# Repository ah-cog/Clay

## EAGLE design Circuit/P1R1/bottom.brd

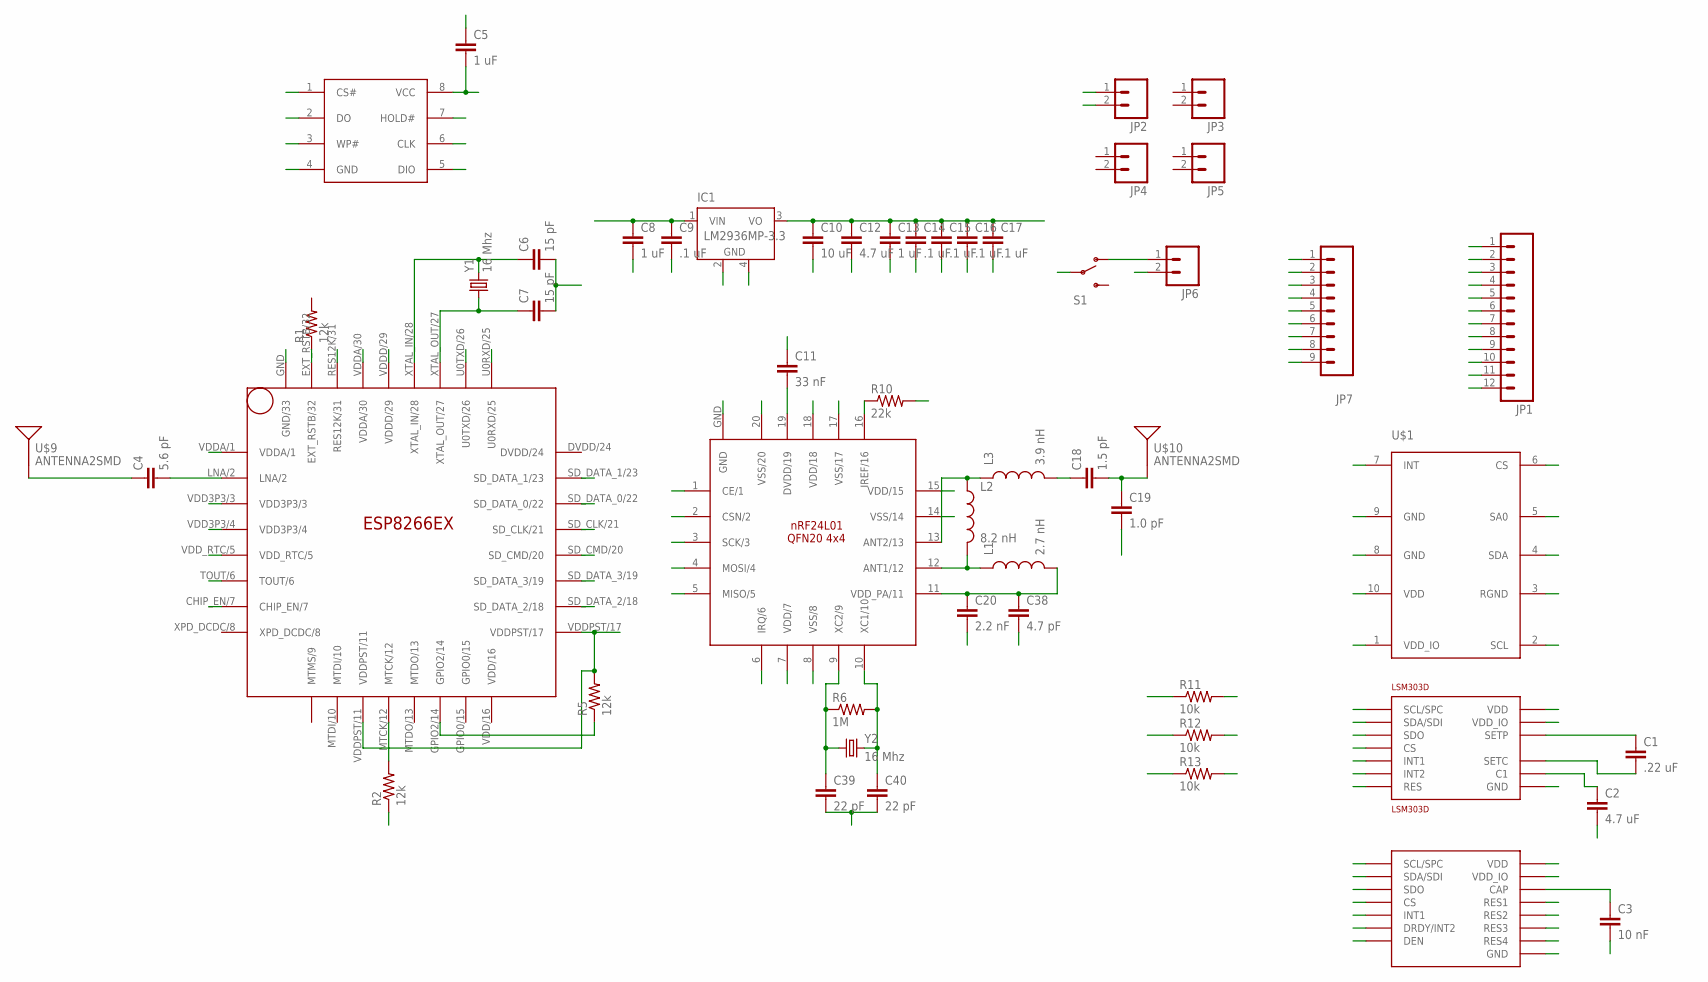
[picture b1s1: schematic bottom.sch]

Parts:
C1: .22 uF; 0603-CAP
C2, C12: 4.7 uF; 0603-CAP
C3: 10 nF; 0603-CAP
C4: 5.6 pF; 0603-CAP
C5, C8, C13: 1 uF; 0603-CAP
C6, C7: 15 pF; 0603-CAP
C9, C14, C15, C16, C17: .1 uF; 0603-CAP
C10: 10 uF; 0603-CAP
C11: 33 nF; 0603-CAP
C18: 1.5 pF; 0603-CAP
C19: 1.0 pF; 0603-CAP
C20: 2.2 nF; 0603-CAP
C38: 4.7 pF; 0603-CAP
C39, C40: 22 pF; 0603-CAP
IC1: LM2936MP-3.3; SOT223
JP1: M12PTH; 1X12
JP2, JP3, JP4, JP5, JP6: M02LOCK; 1X02_LOCK
JP7: M09; 1X09
L1: 2.7 nH; C0402
L2: 8.2 nH; C0402
L3: 3.9 nH; C0402
LSM303D: LSM303D; LGA16L
MESH: NRF24L01; QFN20(4X4)
R1, R2, R5: 12k; 0603-RES
R6: 1M; 0603-RES
R10: 22k; 0603-RES
R11, R12, R13: 10k; 0603-RES
S1: SWITCH-SPDT-SMD-A; SWITCH-SPST-SMD-A
U$1: LPS25H
U$2: L3GD20H; LGA16L
U$3: 25Q40; SOP8
U$9, U$10: ANTENNA2SMD; ANTENNA-CHIP2
WIFI: ESP8266EX; QFN32
Y1, Y2: 16 Mhz; CRYSTAL-SMD-5X3

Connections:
CE: JP7.3, MESH.1 (CE/1)
CSN: JP7.4, MESH.2 (CSN/2)
GND: C2.2, C5.1, C6.2, C7.2, C8.2, C9.2, C10.2, C11.1, C12.2, C13.2, C14.2, C15.2, C16.2, C17.2, C19.2, C20.2, C38.2, C39.2, C40.2, IC1.2 (GND), IC1.4 (GND), JP1.1, JP1.2, JP1.3, JP1.4, JP1.5, JP1.6, JP2.2, JP6.2, LSM303D.P$5 (GND), LSM303D.P$10 (RES), LSM303D.P$12 (GND), LSM303D.P$13 (GND), LSM303D.P$16 (GND), MESH.8 (VSS/8), MESH.14 (VSS/14), MESH.17 (VSS/17), MESH.20 (VSS/20), R2.1, R10.2, U$1.3 (RGND), U$1.8 (GND), U$1.9 (GND), U$2.P$8 (DEN), U$2.P$9 (RES1), U$2.P$10 (RES2), U$2.P$11 (RES3), U$2.P$12 (GND), U$2.P$13 (GND), U$3.4 (GND), WIFI.GND (GND/33)
IQR: MESH.6 (IRQ/6)
MISO: JP7.6, MESH.5 (MISO/5)
MOSI: JP7.5, MESH.4 (MOSI/4)
unnamed: C4.1, U$9.FEED
unnamed: R5.1, WIFI.GPIO2/14
unnamed: R2.2, WIFI.MTCK/12
unnamed: L1.1, L2.2, MESH.12 (ANT1/12)
unnamed: C18.1, L3.2
unnamed: C18.2, C19.1, U$10.FEED
unnamed: C4.2, WIFI.LNA/2
unnamed: C39.1, MESH.9 (XC2/9), R6.1, Y2.1
unnamed: C40.1, MESH.10 (XC1/10), R6.2, Y2.3 (2)
unnamed: C20.1, C38.1, L1.2, MESH.11 (VDD_PA/11)
unnamed: L2.1, L3.1, MESH.13 (ANT2/13)
unnamed: C3.1, U$2.P$14 (CAP)
unnamed: MESH.16 (IREF/16), R10.1
unnamed: C11.2, MESH.19 (DVDD/19)
unnamed: C1.2, LSM303D.P$2 (SETC)
unnamed: C2.1, LSM303D.P$15 (C1)
RST: R1.1, WIFI.EXT_RSTB/32
RTC: WIFI.VDD_RTC/5
RX_W: JP7.1, WIFI.U0TXD/26
SCK: JP7.7, MESH.3 (SCK/3)
SCL: JP7.9, LSM303D.P$4 (SCL/SPC), R12.2, U$1.2 (SCL), U$2.P$2 (SCL/SPC)
SD-CLK: U$3.6 (CLK), WIFI.SD_CLK/21
SD-CMD: U$3.1 (CS#), WIFI.SD_CMD/20
SD-D0: U$3.2 (DO), WIFI.SD_DATA_0/22
SD-D1: U$3.5 (DIO), WIFI.SD_DATA_1/23
SD-D2: U$3.7 (HOLD#), WIFI.SD_DATA_2/18
SD-D3: U$3.3 (WP#), WIFI.SD_DATA_3/19
SDA: JP7.8, LSM303D.P$6 (SDA/SDI), R11.2, U$1.4 (SDA), U$2.P$3 (SDA/SDI)
SDO: LSM303D.P$7 (SDO), R13.2, U$1.5 (SA0), U$2.P$4 (SDO)
SETP: C1.1, LSM303D.P$3 (SETP)
TOUT: WIFI.TOUT/6
TX_W: JP7.2, WIFI.U0RXD/25
VDD: C5.2, C10.1, C12.1, C13.1, C14.1, C15.1, C16.1, C17.1, IC1.3 (VO), JP1.7, JP1.8, JP1.9, JP1.10, JP1.11, JP1.12, JP2.1, LSM303D.P$1 (VDD_IO), LSM303D.P$8 (CS), LSM303D.P$14 (VDD), MESH.7 (VDD/7), MESH.15 (VDD/15), MESH.18 (VDD/18), R5.2, R11.1, R12.1, R13.1, U$1.1 (VDD_IO), U$1.6 (CS), U$1.10 (VDD), U$2.P$1 (VDD_IO), U$2.P$5 (CS), U$2.P$15 (RES4), U$2.P$16 (VDD), U$3.8 (VCC), WIFI.CHIP_EN/7, WIFI.VDD3P3/3, WIFI.VDD3P3/4, WIFI.VDDA/1, WIFI.VDDA/30, WIFI.VDDD/29, WIFI.VDDPST/11, WIFI.VDDPST/17
VIN: JP6.1, S1.1 (O)
VRAW: C8.1, C9.1, IC1.1 (VIN), S1.2
XTAL_IN: C6.1, WIFI.XTAL_IN/28, Y1.3 (2)
XTAL_OUT: C7.1, WIFI.XTAL_OUT/27, Y1.1

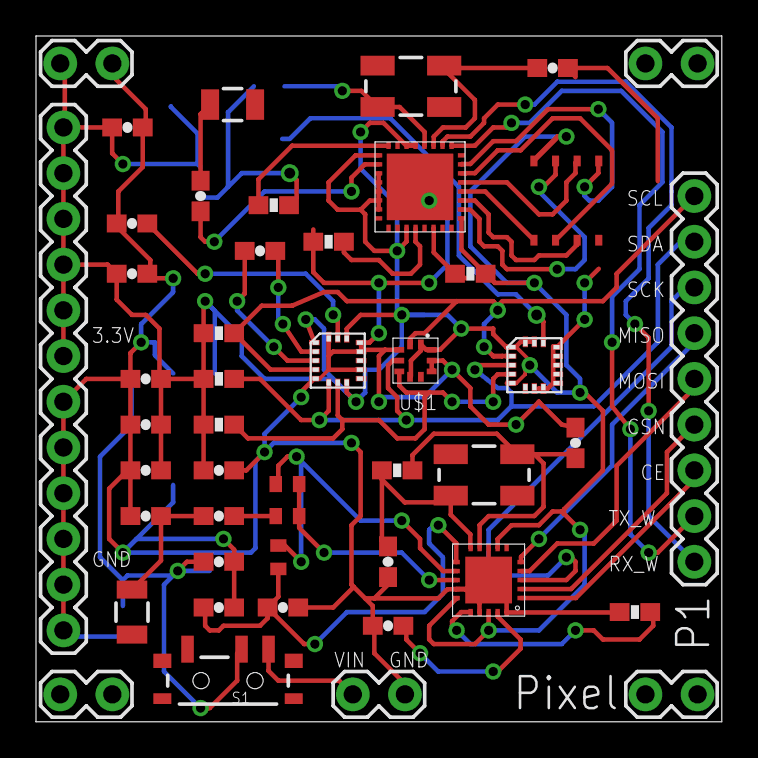
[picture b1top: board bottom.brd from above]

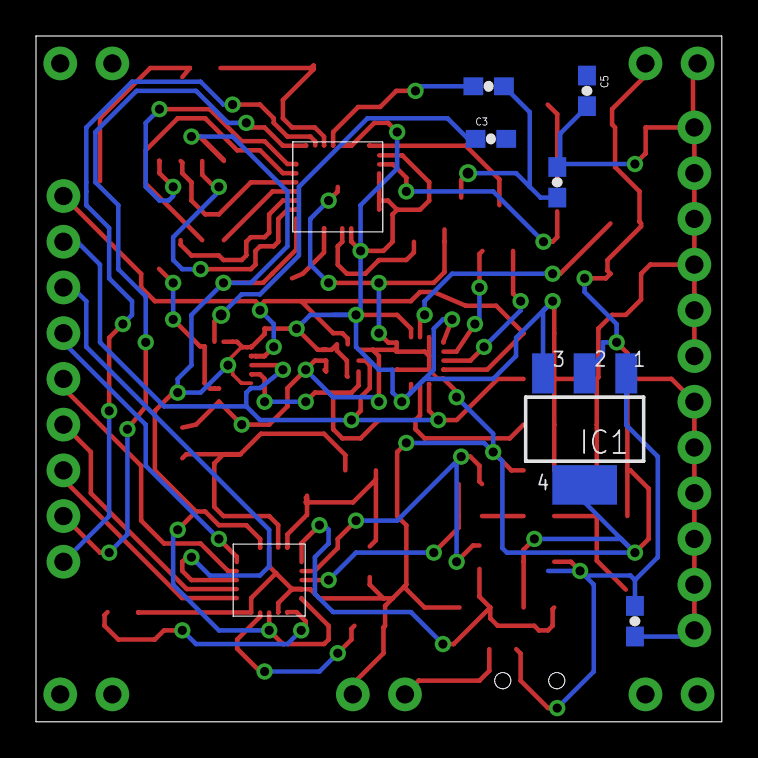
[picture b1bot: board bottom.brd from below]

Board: 2 copper layers, 38.1 x 38.1 mm, 53 parts (6 on the bottom side), 40 nets.

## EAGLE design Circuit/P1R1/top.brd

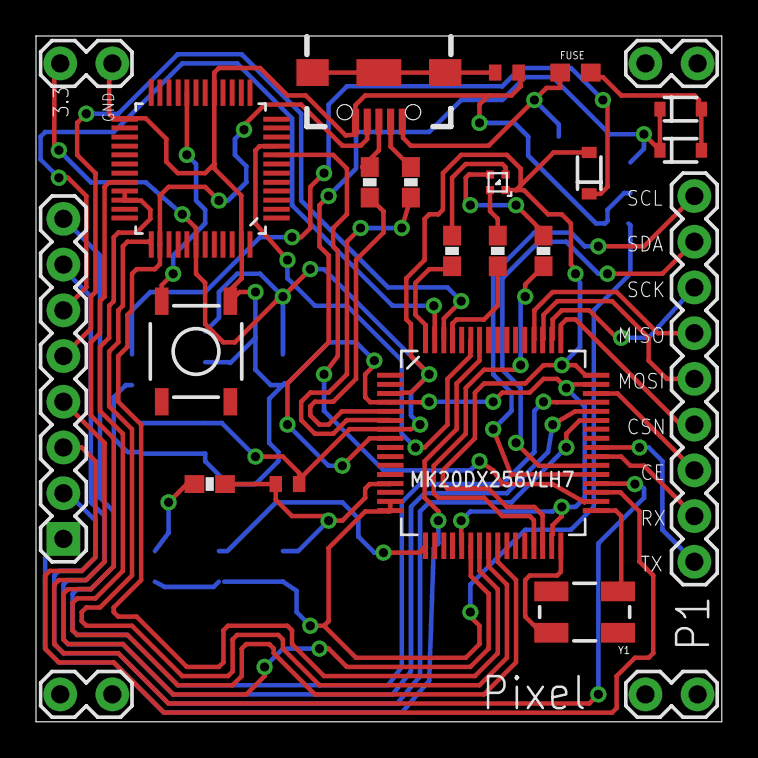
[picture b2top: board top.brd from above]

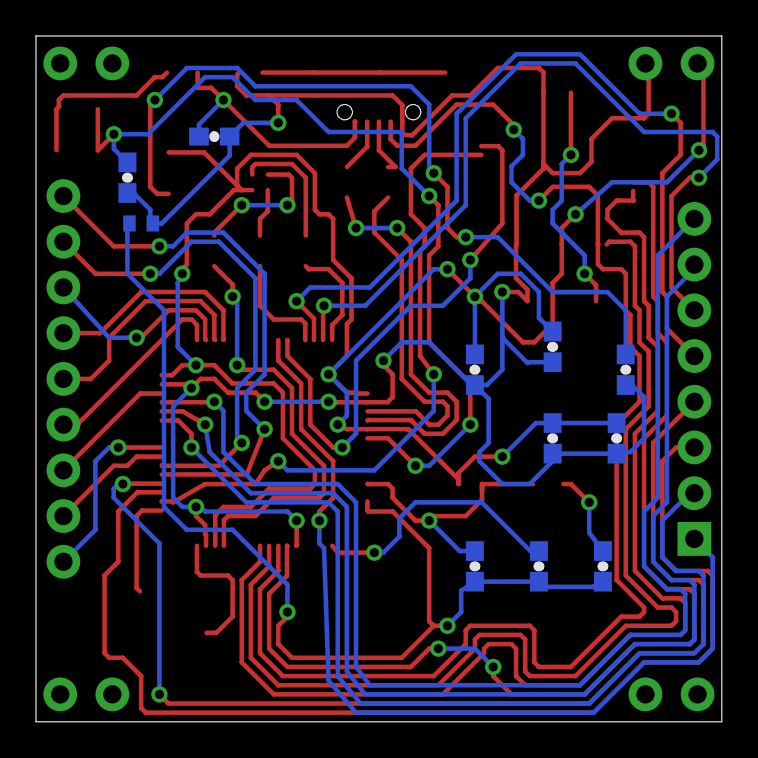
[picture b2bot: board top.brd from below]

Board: 2 copper layers, 38.1 x 38.1 mm, 35 parts (11 on the bottom side), 47 nets.

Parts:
C11, C12, C13, C14, C15, C17, C18, C19, C20: .1 uF; 0603-CAP
C16: 2.2 uF; 0603-CAP
D1: SML-LX0404SIUPGUSB; 1MM_SQ_4PAD
D6, D8, D9: 1A; SOD-323
FERRITE1, FERRITE2, FERRITE3: BLM15HB121SN1; 0402
FUSE: PTC0603; 0603
GPIO: 1X08
JP1: USB-B-MICRO-SMD_V03
JP2, JP5, JP7, JP8: 1X02_LOCK
JP9: 1X09
R1: 470; 0603-RES
R2, R3: 33; 0603-RES
R4, R5, R6: 330; 0603-RES
S1: SWITCH-MOMENTARY-2SMD; TACTILE-SWITCH-SMD
U$2: MK20DX256VLH7; QFP50P1200X1200X160-64N
U$3: MINI54TANDEFAULT; QFP50P900X900X160-48N
Y1: 16 MHz; CRYSTAL-SMD-5X3

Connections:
3.3V: C13.1, C14.1, C15.1, C16.1, D1.1, D6.A, FERRITE1.1, JP2.1, U$2.3, U$2.7, U$2.30, U$2.48, U$3.42
AGND: C17.2, C18.2, C19.2, FERRITE3.2, U$2.15, U$2.16
CE: JP9.3, U$2.46
D+: JP1.D+1, R2.1
D-: JP1.D-1, R3.1
GND-ISO: C11.1, C12.1, C13.2, C14.2, C15.2, C16.2, C20.2, FERRITE2.1, FERRITE3.1, JP1.GND1, JP2.2, S1.1, U$2.4, U$2.21, U$2.31, U$2.47, U$3.17, U$3.25, U$3.47
unnamed: C19.1, U$2.17
unnamed: C12.2, D8.C, D9.C, U$2.8
unnamed: C17.1, FERRITE1.2, R1.1, U$2.13
unnamed: C18.1, R1.2
unnamed: FERRITE2.2, JP1.SHIELD1, JP1.SHIELD2, JP1.SHIELD3
unnamed: S1.3, U$3.20
unnamed: C20.1, D6.C
unnamed: U$2.34, U$3.8
unnamed: JP1.ID1, U$2.23, U$3.38
unnamed: U$2.25, U$3.33, U$3.34
unnamed: U$2.22, U$3.32
unnamed: U$2.24, U$3.37
unnamed: U$2.59, U$3.9
unnamed: R2.2, U$2.5
unnamed: R3.2, U$2.6
unnamed: JP9.4, U$2.49
unnamed: U$2.32, Y1.3
unnamed: U$2.33, Y1.1
unnamed: JP9.5, U$2.51
unnamed: JP9.6, U$2.52
unnamed: GPIO.1, U$2.58
unnamed: GPIO.2, U$2.43
unnamed: GPIO.3, U$2.35
unnamed: D1.3, R4.2
unnamed: D1.4, R5.2
unnamed: D1.2, R6.2
unnamed: GPIO.4, U$2.36
unnamed: GPIO.5, U$2.62
unnamed: GPIO.6, U$2.63
unnamed: GPIO.7, U$2.44
unnamed: GPIO.8, U$2.45
unnamed: R5.1, U$2.64
unnamed: R4.1, U$2.29
unnamed: C11.2, FUSE.1, JP1.VBUS1
unnamed: R6.1, U$2.61
SCK: JP9.7, U$2.50
SCL_T: JP9.9, U$2.37
SDA_T: JP9.8, U$2.38
T_RX: JP9.2, U$2.39
T_TX: JP9.1, U$2.40
VIN: D8.A, D9.A, FUSE.2

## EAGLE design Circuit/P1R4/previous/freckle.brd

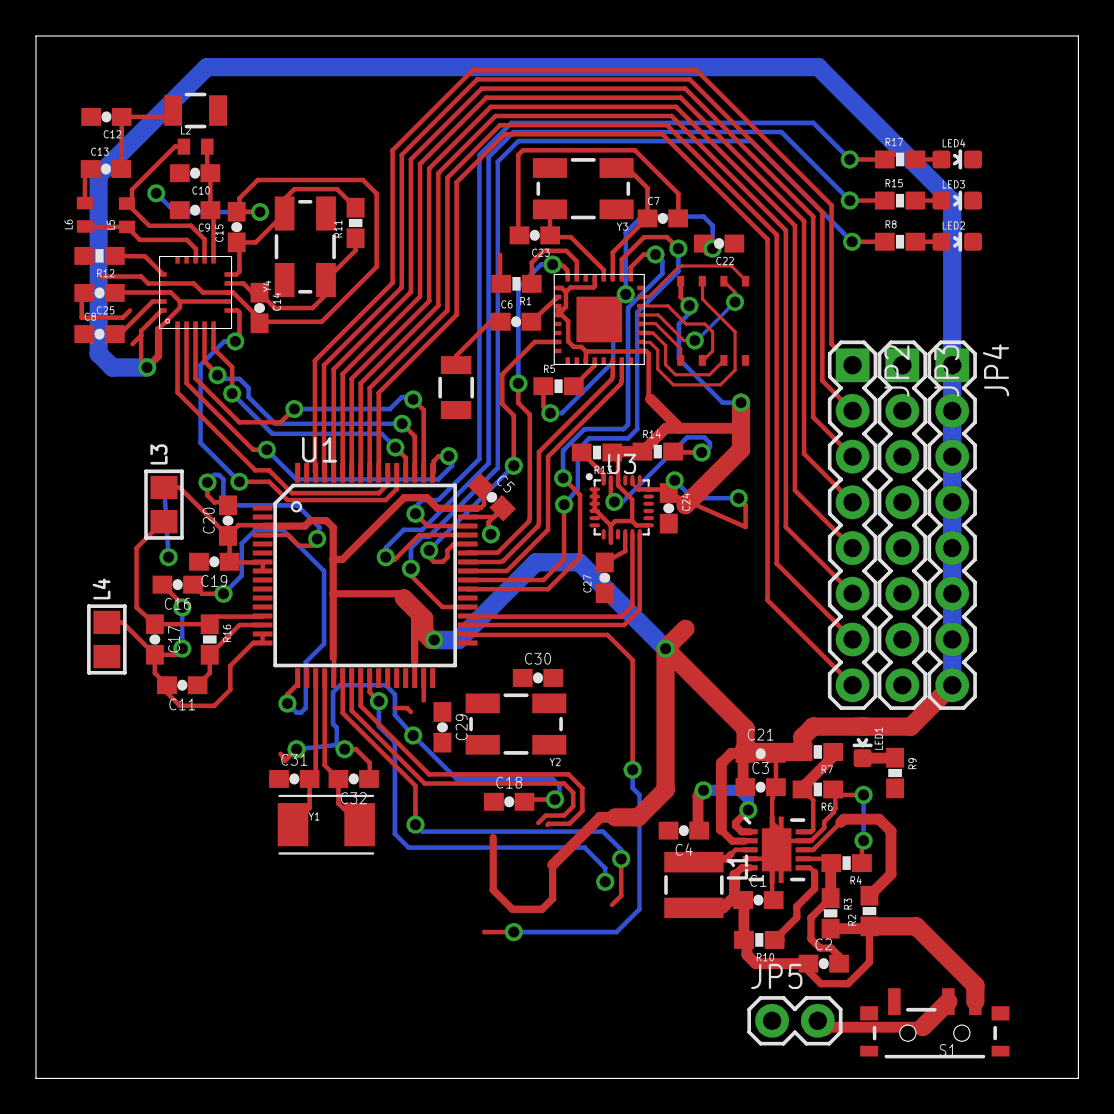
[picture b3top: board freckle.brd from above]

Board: 2 copper layers, 57.9 x 57.9 mm, 74 parts (0 on the bottom side), 71 nets.

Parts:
C1: 10uF; 0603-CAP
C2, C4, C5, C11, C16, C18, C19, C21: 0.1uF; 0603-CAP
C3: 22uF; 0603-CAP
C6: 5.6 pF; 0603-CAP
C7, C23: 15 pF; 0603-CAP
C8: 33 nF; 0603-CAP
C9: 2.2 nF; 0603-CAP
C10: 4.7 pF; 0603-CAP
C12: 1.0 pF; 0603-CAP
C13: 1.5 pF; 0603-CAP
C14, C15, C29, C30, C31, C32: 22 pF; 0603-CAP
C17, C20: 2.2uF; 0603-CAP
C22: 1 uF; 0603-CAP
C24, C25, C27: .1 uF; 0603-CAP
JP2, JP3, JP4: 1X08
JP5: 1X02
L1: 2.2uH, 2.1A; LPS3015
L2: 2.7 nH; C0402
L3, L4: 600 Ohm/100 Mhz; 0805
L5: 8.2 nH; C0402
L6: 3.9 nH; C0402
LED1, LED2, LED3, LED4: LED-0603
R1, R5: 12k; 0603-RES
R2: 10K; 0603-RES
R3: 2M; 0603-RES
R4, R6: 220K; 0603-RES
R7: 1.2M; 0603-RES
R8, R15, R17: 330; 0603-RES
R9, R16: 470; 0603-RES
R10: 1K; 0603-RES
R11: 1M; 0603-RES
R12: 22k; 0603-RES
R13, R14: 10k; 0603-RES
S1: SWITCH-SPST-SMD-A
U1: MK20DX256VLH7
U2: TPS61200; QFN-10_PAD
U3: MPU-9250; QFN-24/3MM
U$1, U$2: ANTENNA2SMD; ANTENNA-CHIP2
U$3: 25Q40; SOP8
U$4: NRF24L01; QFN20(4X4)
U$6: ESP8266EX; QFN32
Y1: 32.768KHz; CRYSTAL-TXC-7A
Y2: 16Mhz/8pF; CRYSTAL-SMD-5X3
Y3: 26 Mhz; CRYSTAL-SMD-5X3
Y4: 16 Mhz; CRYSTAL-SMD-5X3

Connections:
3.3V: C3.1, C5.1, C18.1, C19.1, C20.1, C21.1, C22.2, C24.2, C25.1, JP4.1, JP4.2, JP4.3, JP4.4, JP4.5, JP4.6, JP4.7, JP4.8, L3.2, LED1.A, R7.2, R13.1, R14.1, U1.3, U1.7, U1.8, U1.21, U1.30, U1.48, U2.2, U3.1, U3.8, U3.13, U3.22, U$3.8, U$4.7, U$4.18, U$6.VDD3P3/3, U$6.VDD3P3/4, U$6.VDDA/1, U$6.VDDD/29, U$6.VDDPST/11, U$6.VDDPST/17
FB: R6.2, R7.1, U2.10
GND: C1.2, C3.2, C4.2, C5.2, C7.2, C8.1, C9.2, C10.2, C12.2, C14.2, C15.2, C18.2, C19.2, C20.2, C21.2, C22.1, C23.2, C24.1, C25.2, C27.1, C29.1, C30.1, C31.1, C32.1, JP3.1, JP3.2, JP3.3, JP3.4, JP3.5, JP3.6, JP3.7, JP3.8, JP5.1, L4.1, LED2.C, LED3.C, LED4.C, R1.2, R4.1, R5.1, R6.1, R9.2, R12.2, U1.4, U1.31, U1.47, U2.4, U2.9, U2.11, U2.12, U2.13, U2.14, U2.15, U3.18, U3.20, U$3.4, U$4.8, U$4.17, U$4.20, U$6.GND
unnamed: LED1.C, R9.1
unnamed: L1.1, U2.3
unnamed: LED2.A, R8.2
unnamed: LED3.A, R15.2
unnamed: LED4.A, R17.2
unnamed: C6.2, U$6.LNA/2
unnamed: C6.1, U$1.FEED
unnamed: C14.1, R11.1, U$4.9, Y4.1
unnamed: C15.1, R11.2, U$4.10, Y4.3
unnamed: C9.1, C10.1, L2.2, U$4.11
unnamed: L5.1, L6.1, U$4.13
unnamed: C8.2, U$4.19
unnamed: L2.1, L5.2, U$4.12
unnamed: R12.1, U$4.16
unnamed: C13.1, L6.2
unnamed: C12.1, C13.2, U$2.FEED
unnamed: C29.2, U1.32, Y2.3
unnamed: C30.2, U1.33, Y2.1
unnamed: C31.2, U1.19, Y1.P$2
unnamed: C32.2, U1.20, Y1.P$1
unnamed: R5.2, U$6.MTCK/12
unnamed: C27.2, U3.10
unnamed: R1.1, U$6.RES12K/31
PS: R2.2, U2.8
PTB0: U1.35, U3.12
PTB1: U1.36, U3.11
PTB2: R8.1, U1.37
PTB16: U1.39, U$6.U0RXD/25
PTB17: U1.40, U$6.U0TXD/26
PTB18: U1.41, U$6.GPIO0/15
PTB19: U1.42, U$6.GPIO2/14
PTC0: U1.43, U$6.EXT_RSTB/32
PTC1: U1.44, U$6.CHIP_EN/7
PTC2: R15.1, U1.45
PTC3: R17.1, U1.46
PTC4: U1.49, U$4.2
PTC5: U1.50, U$4.3
PTC6: U1.51, U$4.4
PTC7: U1.52, U$4.5
PTC8: U1.53, U$4.6
PTC9: U1.54, U$4.1
PTC10: JP2.8, U1.55
PTC11: JP2.7, U1.56
PTD0: JP2.6, U1.57
PTD1: JP2.5, U1.58
PTD2: JP2.4, U1.59
PTD3: JP2.3, U1.60
PTD4: JP2.2, U1.61
PTD5: JP2.1, U1.62
SCL: R14.2, U3.23
SD-CLK: U$3.6, U$6.SD_CLK/21
SD-CMD: U$3.1, U$6.SD_CMD/20
SD-D0: U$3.2, U$6.SD_DATA_0/22
SD-D1: U$3.5, U$6.SD_DATA_1/23
SD-D2: U$3.7, U$6.SD_DATA_2/18
SD-D3: U$3.3, U$6.SD_DATA_3/19
SDA: R13.2, U3.24
SOFTPOWER: R10.1, U2.6
UVLO: C2.2, R3.1, R4.2, U2.7
VAUX: C4.1, U2.1
VCC: C1.1, C2.1, L1.2, R2.1, R3.2, R10.2, S1.1, U2.5
VDDA: C17.1, L3.1, R16.1, U1.13
VRAW: JP5.2, S1.2
VREFH: C11.1, R16.2, U1.14
VREFL: C11.2, C16.2, C17.2, L4.2, U1.15, U1.16
VREF_OUT: C16.1, U1.17
XTAL_IN: C23.1, U$6.XTAL_IN/28, Y3.3
XTAL_OUT: C7.1, U$6.XTAL_OUT/27, Y3.1

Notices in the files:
parts and their libraries:
SparkFun-Capacitors: Licensing: Creative Commons ShareAlike 4.0 International - https://creativecommons.org/licenses/by-sa/4.0
